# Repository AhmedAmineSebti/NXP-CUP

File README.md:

# NXP Cup Racing Car

## Overview

The car uses an onboard smart camera to detect track lines, a custom PCB centered on a Teensy 4.1 microcontroller to run the real-time control loops, and a set of IR/ToF sensors for start-line detection and obstacle stopping. This README covers the **mechanical design** and **electronic architecture** of the vehicle.

## Mechanical Design

- Chassis and all mechanical supports designed and modeled in **SolidWorks**.
- **Ackermann steering mechanism**: an **MG996R servo** mounted centrally on the front axle drives both front wheels via a linkage (biellette), so the wheels trace concentric circles in a turn — no lateral scrub.
- **Camera mast**: a raised mount holding the Pixy2 camera for a forward, elevated view of the track.
- **HMI mount**: a dedicated 3D-printed support integrating the OLED display and 2 push buttons.
- Front bumper design integrates 4 IR sensors symmetrically plus a centered ToF sensor.
- Parts were 3D printed; most structural parts in PLA.

## Electronic Architecture

### System Layers

The system is organized in three functional layers around the Teensy 4.1:

- **Perception:** Pixy2 camera (line detection), 4× IR sensors (start/finish line), ToF sensor (obstacle distance)
- **Processing:** Teensy 4.1 — runs two parallel PID loops (steering and speed)
- **Actuation:** MG996R servo (steering), DC motor via H-bridge (propulsion)

### Microcontroller — Teensy 4.1

- ARM Cortex-M7 @ 600 MHz, hardware floating-point unit, 1 MB RAM
- Arduino-compatible, multiple SPI/I²C/UART buses, independent PWM timers
- 35.6 × 17.8 mm footprint, 3.3 V logic level (matches all sensors used)

### Human-Machine Interface (HMI)

- 0.96" OLED display — shows live PID gains and system state
- 2 push buttons — mode selection and race start

### Components Summary

| Component | Reference | Role | Interface |
|---|---|---|---|
| Microcontroller | Teensy 4.1 | Central processing | — |
| Camera | Pixy2 v2 | Line detection | SPI |
| IR sensors | TCRT5000 × 4 | Start/finish line | GPIO |
| ToF sensor | VL53L0X | Obstacle stop | I²C |
| Steering servo | MG996R | Wheel steering | PWM |
| Drive motor | Brushed DC motor | Propulsion | PWM + H-bridge |
| Display | 0.96" OLED | Status display | I²C |
| Buttons | Push button × 2 | Mode selection/Race start | GPIO |
| Wheel encoders | Quadrature, 408 CPR | Speed/position feedback | GPIO (interrupt) |
| Power source | 3S LiPo (12.6 V) | Energy source | — |

### Pinout (Teensy 4.1)

| Pin | Peripheral | Signal | Interface |
|---|---|---|---|
| 12 | Pixy2 Camera | SPI RX (MISO) | SPI0 |
| 11 | Pixy2 Camera | SPI TX (MOSI) | SPI0 |
| 13 | Pixy2 Camera | SPI SCK | SPI0 |
| 10 | Pixy2 Camera | SPI CS | SPI0 |
| 18 | VL53L0X / OLED | I²C SDA | I²C0 |
| 19 | VL53L0X / OLED | I²C SCL | I²C0 |
| 17 | MG996R Servo | PWM | PWM |
| 6-7-22-23 | IBTs | PWM (speed) | PWM |
| 14–17 | IR sensors 1–4 | Start line | GPIO (pull-up) |
| 2-3-4-5 | Rotary encoder | CH A/B | GPIO (interrupt) |
| 8 | Mode button | SW | GPIO |
| 9 | Start button | SW | GPIO |

## Photos

## Repository Contents

- CAD files (chassis, camera mast, steering mechanism, HMI mount)
- PCB design files (KiCad project)
- 3D-printable part files

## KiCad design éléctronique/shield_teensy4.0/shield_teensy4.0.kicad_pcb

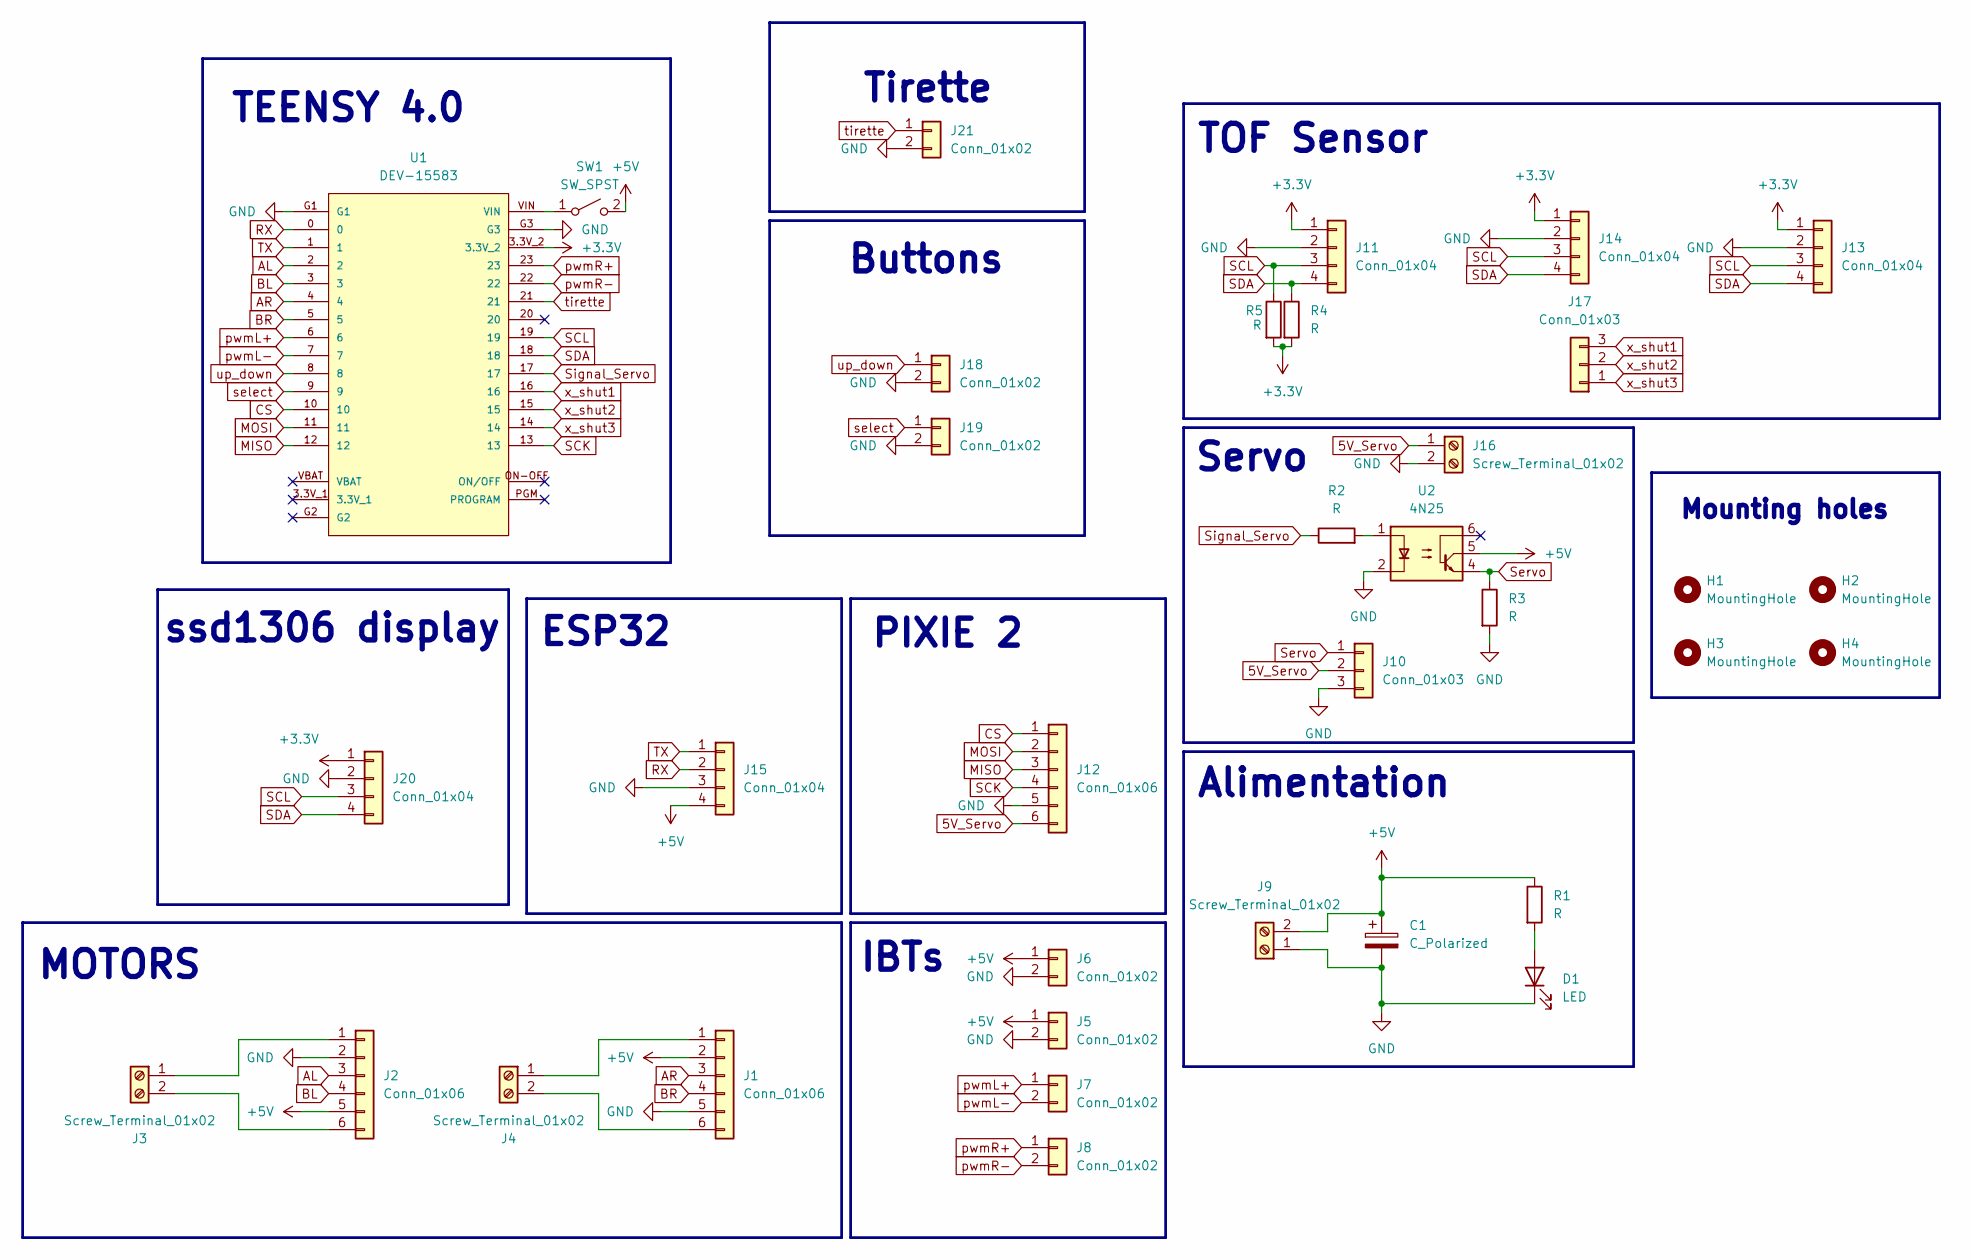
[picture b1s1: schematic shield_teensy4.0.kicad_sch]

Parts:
C1: C_Polarized; CP_Radial_D5.0mm_P2.50mm
D1: LED; LED_D3.0mm
H1, H2, H3, H4: MountingHole; MountingHole_3mm
J1, J2, J12: Conn_01x06; JST_XH_B6B-XH-A_1x06_P2.50mm_Vertical
J3, J4, J9, J16: Screw_Terminal_01x02; TerminalBlock_Phoenix_MKDS-1,5-2_1x02_P5.00mm_Horizontal
J5, J6, J7, J8, J18, J19, J21: Conn_01x02; JST_XH_B2B-XH-A_1x02_P2.50mm_Vertical
J10, J17: Conn_01x03; JST_XH_B3B-XH-A_1x03_P2.50mm_Vertical
J11, J13, J14, J15, J20: Conn_01x04; JST_XH_B4B-XH-A_1x04_P2.50mm_Vertical
R1, R2, R3, R4, R5: R; R_Axial_DIN0204_L3.6mm_D1.6mm_P5.08mm_Horizontal
SW1: SW_SPST; SW_DIP_SPSTx01_Slide_9.78x4.72mm_W7.62mm_P2.54mm
U1: DEV-15583; MODULE_DEV-15583
U2: 4N25; DIP-6_W7.62mm

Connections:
5V_Servo: J10.2, J12.6, J16.1
+3.3V: J11.1, J13.1, J14.1, J20.1, R4.2, R5.2, U1.3.3V_2
+5V: C1.1, J1.2, J2.5, J5.1, J6.1, J9.2, J15.4, R1.1, SW1.2 (B), U2.5
AL: J2.3, U1.2
AR: J1.3, U1.4
BL: J2.4, U1.3
BR: J1.4, U1.5
CS: J12.1, U1.10
GND: C1.2, D1.1 (K), J1.5, J2.2, J5.2, J6.2, J9.1, J10.3, J11.2, J12.5, J13.2, J14.2, J15.3, J16.2, J18.2, J19.2, J20.2, J21.2, R3.2, U1.G1, U1.G3, U2.2
MISO: J12.3, U1.12
MOSI: J12.2, U1.11
unnamed: D1.2 (A), R1.2
unnamed: J1.1, J4.1
unnamed: J1.6, J4.2
unnamed: J2.1, J3.1
unnamed: J2.6, J3.2
unnamed: R2.2, U2.1
unnamed: SW1.1 (A), U1.VIN
RX: J15.2, U1.0
SCK: J12.4, U1.13
SCL: J11.3, J13.3, J14.3, J20.3, R5.1, U1.19
SDA: J11.4, J13.4, J14.4, J20.4, R4.1, U1.18
Servo: J10.1, R3.1, U2.4
Signal_Servo: R2.1, U1.17
TX: J15.1, U1.1
pwmL+: J7.1, U1.6
pwmL-: J7.2, U1.7
pwmR+: J8.1, U1.23
pwmR-: J8.2, U1.22
select: J19.1, U1.9
tirette: J21.1, U1.21
up_down: J18.1, U1.8
x_shut1: J17.3, U1.16
x_shut2: J17.2, U1.15
x_shut3: J17.1, U1.14

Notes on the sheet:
Buttons
MOTORS
Tirette
IBTs
ssd1306 display
Mounting holes
ESP32
Alimentation
Servo
TEENSY 4.0
PIXIE 2
TOF Sensor

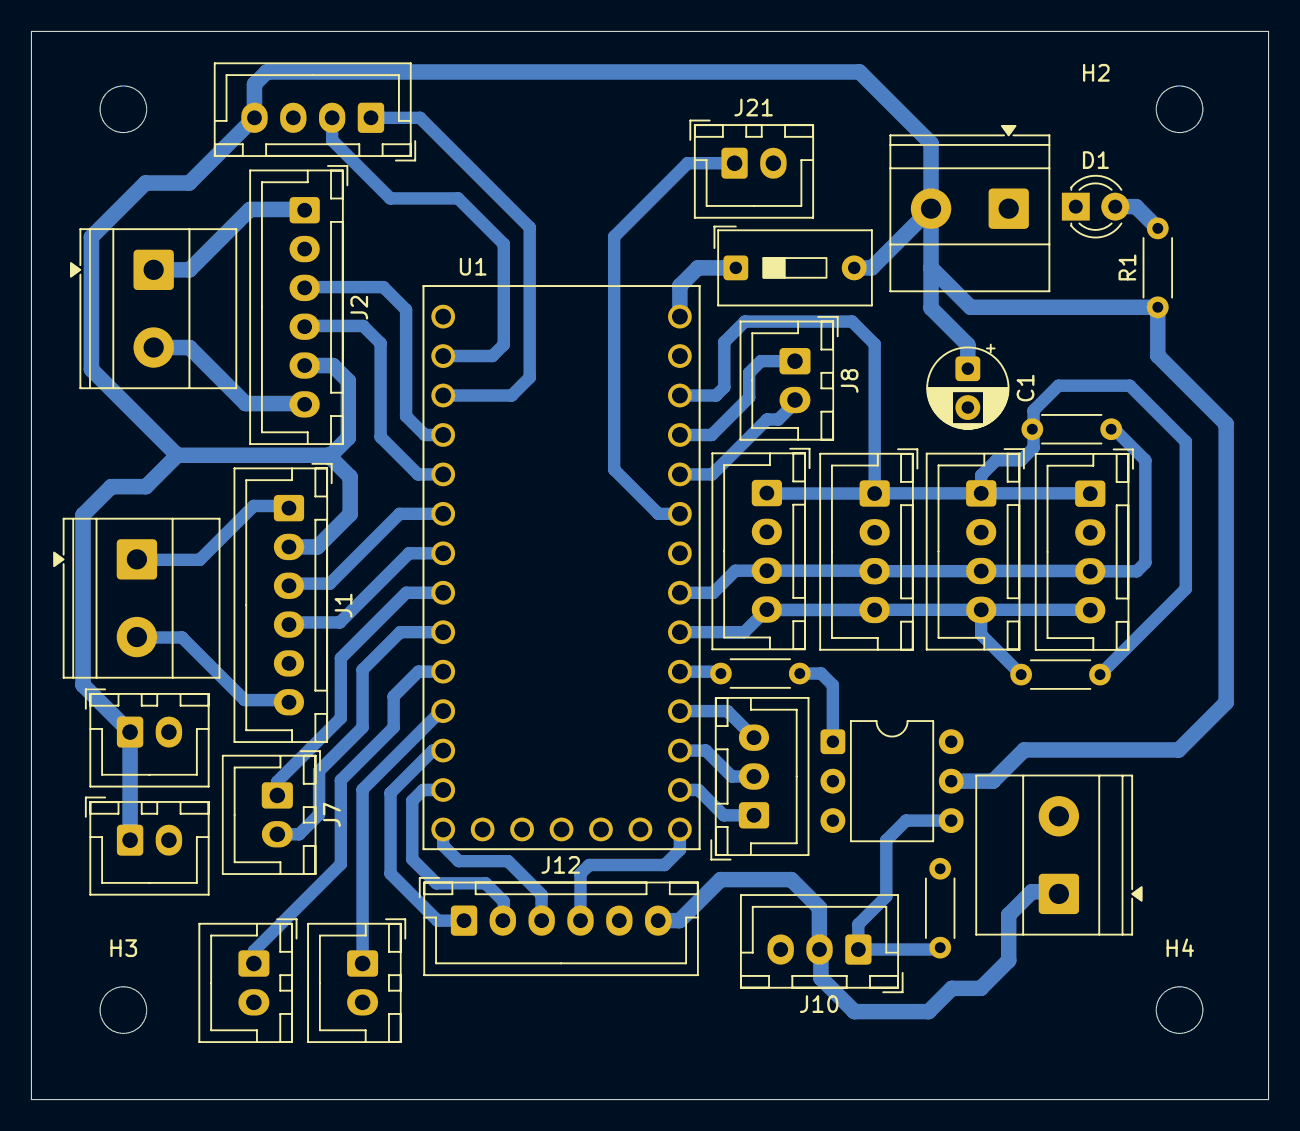
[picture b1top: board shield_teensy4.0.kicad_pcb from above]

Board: 2 copper layers, 79.6 x 68.8 mm, 35 parts (0 on the bottom side), 35 nets.
